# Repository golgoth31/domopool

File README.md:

# Domopool

## Goal

The goal of this project is to automatise some parts of my pool, mainly the flter pump based on the water temperature. There is also an option to use a ph pump.

## Hardware

The base hardware is an esp32 devkitC.
Other hardware:

- Box: [arduitouch](https://www.az-delivery.de/en/products/az-touch-wandgehauseset-mit-touchscreen-fur-esp8266-und-esp32?_pos=4&_sid=61b662d69&_ss=r)
    - LCD: Ili9341 240x320 RGB touch screen
    - Power: Integrated 5V voltage regulator (input voltage 9 - 35V DC)
    - Built-in piezo buzzer
- Controler: [ESP32 board](https://www.az-delivery.de/en/collections/more-products-4/products/esp32-developmentboard)
- Temperatures (water and ambiant): 2 DS18B20
- Water pressure: GS07381-06 (200PSI) [amazon](https://www.amazon.fr/gp/product/B07YZL36FN/ref=ppx_yo_dt_b_asin_title_o06_s00?ie=UTF8&psc=1)
- RTC: DS3231 [amazon](https://www.amazon.fr/gp/product/B07RDHPYJD/ref=ppx_yo_dt_b_asin_title_o08_s00?ie=UTF8&psc=1)
- ADC: ADS1115 [az-delivery](https://www.az-delivery.de/en/products/analog-digitalwandler-ads1115-mit-i2c-interface?_pos=1&_sid=04886a84e&_ss=r)
- LevelShifter: TXS0108E [az-delivery](https://www.az-delivery.de/en/products/logiklevel-wandler-3-3v-5v?_pos=1&_sid=a0a8086aa&_ss=r)
- Relay: 4-relay module 5V with optocoupler low-level trigger [az-delivery](https://www.az-delivery.de/en/products/4-relais-modul?_pos=2&_sid=34a975ef0&_ss=r)

### Pictures

- The box

- The pressure sensor on top of the sand filter

## Funtionalities

- Read/write configuration from preferences (nvs storage)
- Mesure water temperature, ambiant temperature and water pressure
- Auto-detect DS18B20 (temperature sensors)
- Avaluate filtering time based on day hour and water temperature
- Get/Set values through grpc request
- Set time with ntp
- Send data with mqtt
- alarms on temperatures and pressure
- frost protection
- low/high pressure protection

### Configuration

To ease configuration update 2 front-end are under developement:

- CLI: [https://github.com/golgoth31/domopool-cli](https://github.com/golgoth31/domopool-cli)
- UI: [https://github.com/golgoth31/domopool-cli/tree/master/web](https://github.com/golgoth31/domopool-cli/tree/master/web)

### Temp/filter time

The local table is defined like this:

| Temp  |Hour|0  |1  |2  |3  |4  |5  |6  |7  |8  |9  |10 |11 |12 |13 |14 |15 |16 |17 |18 |19 |20 |21 |22 |23 |
|-------|----|:-:|:-:|:-:|:-:|:-:|:-:|:-:|:-:|:-:|:-:|:-:|:-:|:-:|:-:|:-:|:-:|:-:|:-:|:-:|:-:|:-:|:-:|:-:|:-:|
|  t<1  |    | X | X | X | X | X | X | X | X | X | X | X | X | X | X | X | X | X | X | X | X | X | X | X | X |
|1<t<3  |    |   |   |   | X | X |   |   |   |   |   |   |   |   |   |   |   |   |   |   |   |   |   |   |   |
|3<t<6  |    |   |   |   | X | X |   |   |   |   |   |   |   |   |   |   |   |   |   |   |   |   |   |   |   |
|6<t<9  |    |   |   |   |   | X | X |   |   |   |   |   | X |   |   |   |   |   |   |   |   |   |   |   |   |
|  t=6  |    |   |   |   |   | X | X |   |   |   |   |   | X |   |   |   |   |   |   |   |   |   |   |   |   |
|  t=7  |    |   |   |   |   |   | X |   |   |   |   | X | X |   |   |   |   |   |   |   |   |   |   |   |   |
|  t=8  |    |   |   |   |   |   |   |   |   |   |   | X | X |   |   | X |   |   |   |   |   |   |   |   |   |
|  t=9  |    |   |   |   |   |   |   |   |   |   | X | X | X |   |   | X |   |   |   |   |   |   |   |   |   |
|9<t<12 |    |   |   |   |   |   |   |   |   | X | X | X |   |   |   | X |   |   |   |   |   |   |   |   |   |
|12<t<15|    |   |   |   |   |   |   |   |   | X | X | X |   |   |   | X | X |   |   |   |   |   |   |   |   |
|15<t<18|    |   |   |   |   |   |   |   |   | X | X | X |   |   |   | X | X | X |   |   |   |   |   |   |   |
|18<t<21|    |   |   |   |   |   |   |   |   | X | X | X | X |   |   | X | X | X |   |   |   |   |   |   |   |
|21<t<23|    |   |   |   |   |   |   |   |   | X | X | X | X |   |   | X | X | X | X |   |   |   |   |   |   |
|23<t<26|    |   |   |   | X | X |   |   |   | X | X | X | X |   |   | X | X | X | X | X |   |   |   |   |   |
|26<t<28|    |   |   |   | X | X | X |   |   | X | X | X | X |   |   | X | X | X | X | X | X |   |   |   |   |
|28<t<30|    |   |   |   | X | X | X | X |   | X | X | X | X |   |   | X | X | X | X | X | X | X |   |   |   |
|30<t   |    | X | X | X | X | X | X | X | X | X | X | X | X | X | X | X | X | X | X | X | X | X | X | X | X |

Other table exemples:

- from [1](https://pool-technologie.com/fichiers/spec_telechargement/MANUEL%20SIMPLEO-FR.pdf)

- from [https://www.piscine-center.net/gestion-de-la-filtration-et-de-l-electrolyseur.html](https://www.piscine-center.net/gestion-de-la-filtration-et-de-l-electrolyseur.html)

- from [https://www.perfeco-f.fr/index.php/le-perfeco](https://www.perfeco-f.fr/index.php/le-perfeco)

## ToDo

- set hour if ntp and rtc are not ok
- add Hbridge driver for peristaltic pump (ph)
- add ability to redefine filter pump steps

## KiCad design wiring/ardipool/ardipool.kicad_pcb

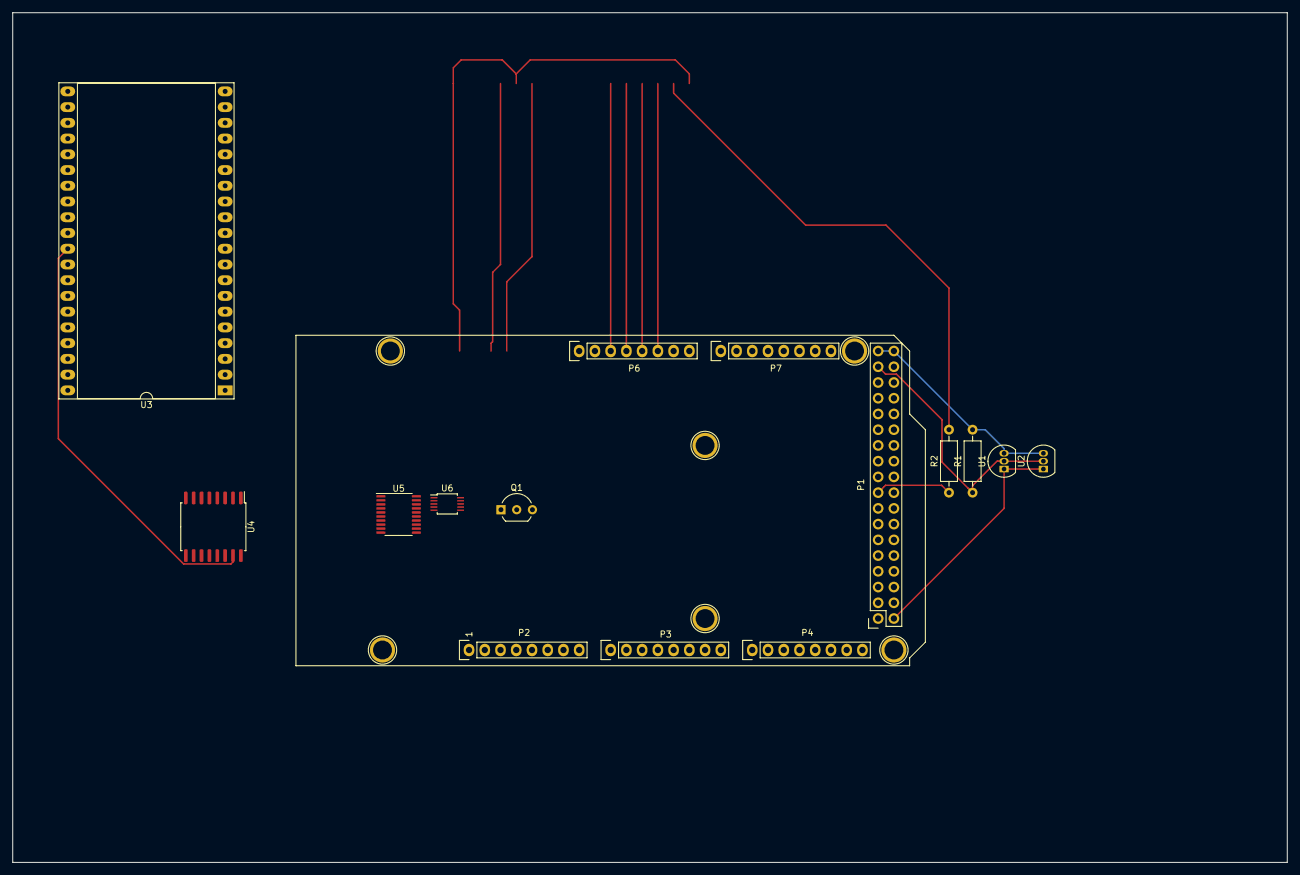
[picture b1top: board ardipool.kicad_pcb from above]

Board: 2 copper layers, 205.7 x 137.2 mm, 21 parts (0 on the bottom side), 16 nets.

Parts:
P1: Digital; Socket_Strip_Arduino_2x18
P2: Power; Socket_Strip_Arduino_1x08
P3, P4: Analog; Socket_Strip_Arduino_1x08
P6: PWM; Socket_Strip_Arduino_1x08
P7: Communication; Socket_Strip_Arduino_1x08
P8, P9, P10, P11, P12, P13: CONN_01X01; Arduino_1pin
Q1: BC557; TO-92_Inline_Wide
R1: 4.7k; R_Axial_DIN0207_L6.3mm_D2.5mm_P10.16mm_Horizontal
R2: 1K; R_Axial_DIN0207_L6.3mm_D2.5mm_P10.16mm_Horizontal
U1, U2: DS18B20; TO-92_Inline
U3: ESP32devkitC; DIP-40_W25.4mm_Socket_LongPads
U4: DS3231M; SOIC-16W_7.5x10.3mm_P1.27mm
U5: TXS0108EPW; TSSOP-20_4.4x6.5mm_P0.65mm
U6: ADS1115IDGS; TSSOP-10_3x3mm_P0.5mm

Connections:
+3V3: P2.4, Q1.3, R1.2, U1.3, U2.3, U3.22, U4.2, U5.2
+5V: P1.35, P1.36, P2.5, U3.40, U5.19
DS18B20: P1.33, R1.1, U1.2, U2.2, U3.25
GND: P1.1, P1.2, P2.6, P2.7, U1.1, U2.1, U3.13, U3.19, U3.35, U4.5, U4.6, U4.7, U4.8, U4.9, U4.10, U4.11, U4.12, U4.13, U5.11
LED_32: R2.2, U3.4
unnamed: Q1.2, R2.1
unnamed: U5.12, U6.2
unnamed: U5.13, U6.1
unnamed: U5.14, U6.9
unnamed: U5.15, U6.10
Relay1-Filter: U3.36, U5.1
Relay2-ph: U3.37, U5.3
Relay3-ch: U3.38, U5.4
Relay4-light: U3.39, U5.5
SCL: P7.8, U3.32, U4.16, U5.6
SDA: P7.7, U3.31, U4.15, U5.7

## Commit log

2020-05-05 make public
2020-05-05 Set theme jekyll-theme-slate
2020-05-06 post config ok
2020-05-06 update temp table in readme
2020-05-06 lock filter pump on by 1 hour step
2020-05-06 add 1h step on filter pump
2020-05-07 first test for esp32
2020-05-09 start to add esp32 remove dht; use ds18b20 as ambiant temperature
2020-05-09 cleaning
2020-05-11 fix pump add alarm
2020-05-14 adjuste config (nothing work for now)
2020-05-14 update gitignore
2020-05-15 begin menu
2020-05-15 start menu page
2020-05-18 schem
2020-05-18 feat: Add electro ch if temp over 15 for 3 days
2020-05-19 start moving to esp32
2020-05-20 refactor: Rem code for mega
2020-05-24 update to esp32
2020-06-01 tests
2020-06-01 start ota add webthing interface
2020-06-02 prepare platform.ini for ota
2020-06-02 OTA !
2020-06-03 start define webthings
2020-06-03 working first things
2020-06-05 fix tft_espi
2020-06-07 first screen
2020-06-10 make display working
2020-06-17 add test values
2020-06-18 fix chon down when filter pump down
2020-06-19 mv to async web server
2020-06-20 update web service
2020-06-21 test of spiffs
2020-06-22 rem storage lib
2020-06-22 ts on reading file
2020-06-22 json read bug ...
2020-06-23 mv conf from arduinojson to preferences
2020-06-23 use prefs add api route for filter
2020-06-24 fix automatic pump switching add mqtt for metrics
2020-06-25 use default for prefs
2020-06-25 remove eeprom calls in sensors
2020-06-25 rem all eeprom
2020-06-26 update post handler for filter and mqtt
2020-06-26 update display
2020-06-26 fix keeping state when switching from automatic mode
2020-06-26 update api
2020-06-27 add beep on touch
2020-06-28 add cors header
2020-06-29 update cors
2020-06-29 found bug in pref lib workaround on this bug
2020-06-30 test on prefs
2020-07-07 update network
2020-07-07 add uplaod route for ui
2020-07-15 various fix and update make rtc working start phy cable
2020-07-16 make use of config.states
2020-07-21 clean ini
2020-07-22 clean
2020-07-22 use proto
2020-07-22 use proto (#1)
2020-07-23 mv proto to own repo
2020-07-24 quick fix
2020-07-26 send protobuf
2020-07-27 start to remove all arduinojson call
2020-07-28 update proto
2020-08-03 rem arduinojson usage
2020-08-03 update duration
2020-10-25 add water-pressure
2020-12-26 feat: Working without pressure
2020-12-27 fix: Various
2020-12-28 fix: Change to default on filter api
2020-12-30 feat: Chg ads1x15 lib
2020-12-30 feat: Debug ads1115
2020-12-30 fix: Water pressure
2020-12-31 feat: Chg ads request from continuous to one shot
2021-01-02 feat: Add alarms on wp and autocalibration
2021-01-04 refactor: Small refactor on filter pump
2021-01-08 fix: Various fixes
2021-01-11 fix: Text size for negative values in display
2021-01-12 feat: Update network if no wifi
2021-01-12 fix: Enhance network
2021-01-13 fix: Fix network connect/disconnect
2021-01-15 feat: Bump proto
2021-01-17 feat: Add enable/disable on wp display
    Send mqtt messages as json
2021-01-19 feat: Bump to proto v1.0.35 for adc config
2021-01-19 feat: Add mqtt
2021-01-20 docs: Update readme
2021-01-21 fix: Mqtt client
2021-01-21 fix: Test on wp
2021-01-22 feat: Add network to set adc config
2021-01-22 feat: Test on pressure
2021-01-22 fix: Wp by changing gain
    Set adc param for each measure
2021-01-23 fix: Pressure and filter
    Slowdown adc to improve pressure precision
    Fix filter start/atop/auto
2021-01-24 fix: Pump table
2021-01-25 feat: Add timestamp to metrics
    Fix ntp usage
2021-01-25 fix: Try to fix mqtt alarms not sent
2021-01-25 feat: Fix mqtt alarms
2021-01-26 fix: Reste alarms
2021-01-26 fix: Wp auto cal
2021-01-27 feat: Blank wp when starting filter
2021-01-28 fix: Hours for pump
2021-02-08 docs: Add pictures
2021-02-08 docs: Better box description
2021-02-26 feat: Add watchdog
2021-02-27 fix: Reset wdt each 2s
2021-03-03 fix: Wdt duration in config
2021-03-22 feat: Chg time to string in metrics
2021-03-30 fix: Force filter pump
2021-04-09 feat: Update deps
2021-04-24 feat: Add recover mode
    Fix states
2021-04-25 fix: Typo on pump variables
2021-05-03 feat: Use latest proto
    Rewrite ch start based on temp
2021-05-04 fix: Add temp sensors info to config
2021-05-21 feat: Bump some libs
2021-05-31 feat: Update libs
2021-06-25 fix: Bump time library
2021-06-25 feat: Unify filter, ch and ph api route
2021-06-25 feat: Add all relay action
2021-06-29 fix: Filter
2021-07-22 feat: Simplify relay start/stop
2021-07-25 feat: Toggle auto/recover mode
2021-09-15 feat: Bump arduinojson
2021-10-25 feat: Updates
2021-10-25 feat: Simplify mqtt message
2021-11-28 fix: Json for states mqtt message
2021-12-12 feat: Bump libs
2022-03-27 feat: Mv default saved twater to 14
2022-05-17 feat: Create 3 automatic mode: dynamic, half day, full day
2022-05-17 chore: Chg button name
2022-05-30 feat: Save twater when filter switch off
2022-06-06 feat: Mv wp to integer
2022-11-13 fix: Display and pressure
2026-02-22 Add renovate.json
2026-02-22 Add renovate.json (#2)
